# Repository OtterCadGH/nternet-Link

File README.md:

# nternet-Link

**An open-hardware platform that turns a TI-Nspire graphing calculator into a
networked handheld terminal.** It adds Wi-Fi, an AI chat/tutor, a camera that
reads and solves problems, and onboard storage, all through a small plug-in
device.

New to the Nspire scene? The spelling "nternet" is intentional. The Nspire's name plays on "inspire", and community projects follow suit by dropping the first letter, like the Ndless jailbreak playing on "endless". nternet is "internet", Nspire style.

Over four generations the project grew from a soldered-in modification into a
clean, reproducible, plug-in platform with a proper communication protocol and
custom PCBs.

[Discord](https://discord.gg/bBMqzaBu6B) · [Support on Ko-fi](https://ko-fi.com/nspired_hackers)

> **Not affiliated with or endorsed by Texas Instruments.** This is an
> embedded-systems and networking experiment. It is **not** designed or
> intended for use during exams. Follow your institution's rules.

---

## Try the calculator interface in your browser

The V4 calculator UI runs as a live simulator. The on-screen calculator and a
virtual ESP32 talk over the *real* V4 wire protocol, so you can experiment with
the whole experience before building anything.

**[Open the live simulator](https://ottercadgh.github.io/nternet-Link/v4/tools/gui_simulator.html)**,
or download [`v4/tools/gui_simulator.html`](v4/tools/gui_simulator.html) and
open it in any browser (it runs fully offline).

---

## Which version should I look at?

**Build [V4](v4/). It is the current, recommended generation.** The others are
here as history and reference.

| | Version | What it is | Build it? |
| --- | --- | --- | --- |
| 🟢 | **[V4](v4/)** | Rewritten firmware, protocol, and UI. Two custom PCBs: a full **camera** stick and a tiny **chat-only** board. Browser simulator, automated tests. | **Yes, start here** |
| ⚪ | [V3](v3/) | First ESP32-S3 and camera platform, with a host proxy server. | Superseded |
| ⚪ | [V2](v2/) | First external USB plug-in adapter (ESP32-C3). No calculator mod. | Superseded |
| ⚪ | [V1](v1/) | The original: an ESP32 soldered *inside* the calculator. | Legacy / reference |

---

## How it works

```
 TI-Nspire  =USB=>  nternet-Link device  =Wi-Fi=>  AI provider
 (keyboard,         (ESP32 + USB bridge             (Groq / OpenAI /
  screen, Lua)       + camera + SD)                  OpenRouter / local)
```

The calculator supplies the keyboard and screen and runs a Lua app. The device
is an ESP32 that bridges USB-serial to Wi-Fi, calls an AI API, drives a camera,
and stores photos and chat logs on a microSD card. In V4 the two sides speak
**nlink v1**, a framed protocol with CRC checks and automatic retries.

---

## Repository layout

```
README.md          you are here: the project hub
docs/              shared assets (hub images)
v1/                Ti-GPT, internal mod (legacy)
   firmware/       ESP32 .ino
   calculator/     Lua app + .tns
v2/                external adapter (docs)
v3/                ESP32-S3 and camera platform
   firmware/       ESP32 .ino
   calculator/     Lua app + .tns
   server/         host proxy server
v4/                CURRENT: the full rewrite
   README.md       tutorial and build guide (start here)
   src/ include/   ESP32 firmware (C++)
   calculator/     TI-Nspire Lua client + demo
   tools/          browser GUI simulator
   docs/           protocol spec
   test/           host-side tests
   hardware/       PCB design + 4 KiCad board variants
```

Each version folder has its own README. New here? Open [`v4/`](v4/).

---

## The story

**V1 (2025)** proved the concept by soldering an ESP32 onto the calculator's
USB lines. **V2** moved all the electronics *outside* into a plug-in adapter,
with no calculator modification. **V3** jumped to the ESP32-S3 with a camera
and a host proxy. **V4** is the ground-up rewrite: a reliable checksummed
protocol, no API keys in the source (they live in the device's flash), support
for any OpenAI-compatible AI provider, a browser simulator, automated tests,
and two custom circuit boards.

## Support

nternet-Link is a small side project, built in spare time and shared for free.
If it's been useful to you and you'd like to chip in, tips go toward parts and
the first run of ready made cables. No pressure at all, and thank you either way.

## License and spirit

Open hardware and software. Modify, improve, and share. Built for learning
about USB, serial protocols, embedded networking, and hardware interfacing.

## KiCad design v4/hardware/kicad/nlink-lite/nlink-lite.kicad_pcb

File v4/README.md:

# nternet-Link V4

**Turn a TI-Nspire graphing calculator into a networked handheld terminal.**
It adds Wi-Fi, an AI chat/tutor, a camera that reads and solves problems, and a
microSD card, all through a tiny plug-in device. No calculator modification.

V4 is a ground-up rewrite of the firmware, the calculator software, the
communication protocol, and the hardware, with two board designs: a full
camera stick and a tiny chat-only "stealth" version.

> **Not affiliated with Texas Instruments.** This is an embedded-systems and
> networking experiment. It is **not** designed or intended for use during
> exams. Follow your school's rules. Don't be that guy.

---

## Try it first: the calculator UI runs in your browser

Before you build anything, you can play with the exact interface the
calculator runs. This simulator is the *real* thing: the on-screen
calculator and a virtual ESP32 talk to each other over the actual V4 wire
protocol, byte for byte.

### [Open the live simulator](https://ottercadgh.github.io/nternet-Link/v4/tools/gui_simulator.html)

*(That live link works once GitHub Pages is enabled. See
[Publish the demo](#publish-the-demo-optional) below. Until then, download
[`tools/gui_simulator.html`](tools/gui_simulator.html) and double-click it.
It runs fully offline in any browser.)*

### What to try in it

1. **Click the calculator screen** to give it keyboard focus.
2. Press **`W`**, pick a Wi-Fi network, type any password, press **Enter**.
   (It's simulated, so any password "connects.")
3. Press **`T`**, type a question like `derivative of x^2`, press **Enter**,
   and watch the orange spark "think," then the answer stream in.
4. Press **Enter** on its own to "take a photo." A photo card appears and a
   solved problem streams back. Check the **SD card** panel: `IMG_0001.JPG`
   just appeared, exactly as it would on the real device.
5. Now break things on purpose with the **Virtual ESP32** panel:
   - **Corrupt next frame**: watch the wire log reject a bad packet and
     recover. This is the V4 protocol's error-checking working live.
   - **Force BUSY**, **API error**, **Drop WiFi**, **Unplug device**: see
     how the UI handles each.

The **Wire log** on the right shows every message between calculator and
device, decoded. That's the whole point of V4: a reliable, checksummed link.

---

## The four generations (and where V4 fits)

| Version | What it is | Status |
| ------- | ---------- | ------ |
| V1 Ti-GPT | ESP32 soldered *inside* the calculator | Legacy / historical |
| V2 nternet-Link | External USB plug-in adapter (ESP32-C3) | Works |
| V3 | ESP32-S3 plus camera, first modular platform | Superseded by V4 |
| **V4 (this)** | Rewritten firmware, protocol, and UI, two custom PCBs | **Current** |

**What V4 fixes from V3:** a proper checksummed packet protocol (no more
garbled responses), **no API keys baked into the source** (they live in the
device's flash, set from the calculator), support for any OpenAI-compatible AI
provider, and a clean, modular codebase with automated tests.

---

## How it works (the 30-second version)

```
 TI-Nspire  =USB=>  nternet-Link device  =Wi-Fi=>  AI provider
 (keyboard,         (ESP32 + USB bridge             (Groq / OpenAI /
  screen, Lua)       + camera + SD)                  OpenRouter / local)
```

The calculator runs a Lua app (its keyboard and screen). The device is an
ESP32 that bridges USB-serial to Wi-Fi, talks to an AI API, drives a camera,
and saves photos and chats to a microSD card. They communicate over **nlink
v1**, a small framed protocol with CRC checks and automatic retries
([full spec](docs/PROTOCOL.md)).

---

## Two boards to build

| | **nlink-cam** | **nlink-lite** |
| --- | --- | --- |
| MCU | ESP32-S3-PICO-1 (SiP) | ESP32-C3-MINI-1 |
| Features | AI chat **plus camera plus microSD** | AI chat only |
| Size | about 60 x 12.5 mm stick | about 38 x 16 mm, tiny |
| Use it for | The full experience | Minimal / discreet |

Both are in [`hardware/kicad/`](hardware/kicad/) as complete, netlist-verified
KiCad projects. Two more reference designs (`nlink-proto` on the S3-MINI-1
module, `nlink-stick` bare-chip) are included as build and de-risking variants.
See [`hardware/PCB-DESIGN.md`](hardware/PCB-DESIGN.md) for the full spec and
[`hardware/kicad/CAPTURE-PLAN.md`](hardware/kicad/CAPTURE-PLAN.md) for the
board internals.

---

## Build guide

### 1. Get the hardware

Start from a dev board to try everything before committing to a custom PCB.
A **Seeed XIAO ESP32-S3 (Sense)** gives you the S3, camera, and SD in one
module. You'll also need a **CP2102/CP2102N USB-UART bridge** and a
**USB-mini plug** to reach the calculator's port. Full parts list and wiring
in [`hardware/PCB-DESIGN.md`](hardware/PCB-DESIGN.md).

### 2. Flash the firmware

The firmware uses [PlatformIO](https://platformio.org/) (free VS Code
extension). Clone this folder, open it, and build the target for your board:

```bash
pio run -e xiao-s3    -t upload    # XIAO ESP32-S3 dev board (camera + SD)
pio run -e nlink-cam  -t upload    # custom camera PCB (ESP32-S3-PICO-1)
pio run -e nlink-lite -t upload    # custom chat-only PCB (ESP32-C3-MINI-1)
```

No secrets go in the code. You'll set your Wi-Fi and AI key **from the
calculator** in the next step.

### 3. Load the calculator app

Copy the Lua app onto your calculator with the free **TI-Nspire Student
Software** (or TiLP). The client library is
[`calculator/nlink.lua`](calculator/nlink.lua) and a ready-to-run app is
[`calculator/demo_app.lua`](calculator/demo_app.lua). Build them into a
`.tns` file and send it to the calculator.

### 4. First run

1. Plug the device into the calculator, open the app.
2. Get a free AI key (for example from [Groq](https://console.groq.com/keys)).
3. On the calculator, set it once. It's saved to the device's flash:
   ```
   CFG SET llm.key   YOUR_KEY_HERE
   CFG SET llm.base  https://api.groq.com/openai/v1
   ```
4. Press **`W`** to pick your Wi-Fi and enter the password.
5. Press **`T`** to ask a question, or **Enter** to snap a photo of a
   problem. Answers save to the SD card automatically.

Everything you'll see on screen is exactly what the
[browser simulator](#try-it-first-the-calculator-ui-runs-in-your-browser)
above shows.

---

## Repository layout

```
platformio.ini        firmware build targets
include/  src/         ESP32 firmware (C++): protocol, provisioning,
                       AI client, camera, SD storage
calculator/            TI-Nspire Lua client library + demo app
tools/gui_simulator.html   the browser demo above
docs/PROTOCOL.md       nlink v1 wire-protocol spec
test/                  host-side protocol tests (run on a PC)
hardware/              PCB design docs + 4 KiCad board variants
PROJECT-STATUS.md      current status and next steps
```

---

## Publish the demo (optional)

To make the browser simulator open from a link (so people can try it without
downloading), turn on **GitHub Pages**:

1. Repo **Settings**, then **Pages**.
2. **Build and deployment**, **Source: Deploy from a branch**.
3. Pick the branch this folder lives on and **/ (root)**, then **Save**.
4. After a minute, your simulator is live at:
   `https://ottercadgh.github.io/nternet-Link/v4/tools/gui_simulator.html`

Then the **Open the live simulator** button near the top of this page just
works.

---

## Status and roadmap

See [`PROJECT-STATUS.md`](PROJECT-STATUS.md). Short version: firmware,
protocol, simulator, and all four board schematics are done and verified.
Next up is finishing the custom-PCB layouts, porting the new UI onto the
calculator, and a first hardware bring-up.

## License and spirit

Open hardware and software. Modify, improve, and share. Built for learning
about USB, serial protocols, embedded networking, and hardware interfacing.

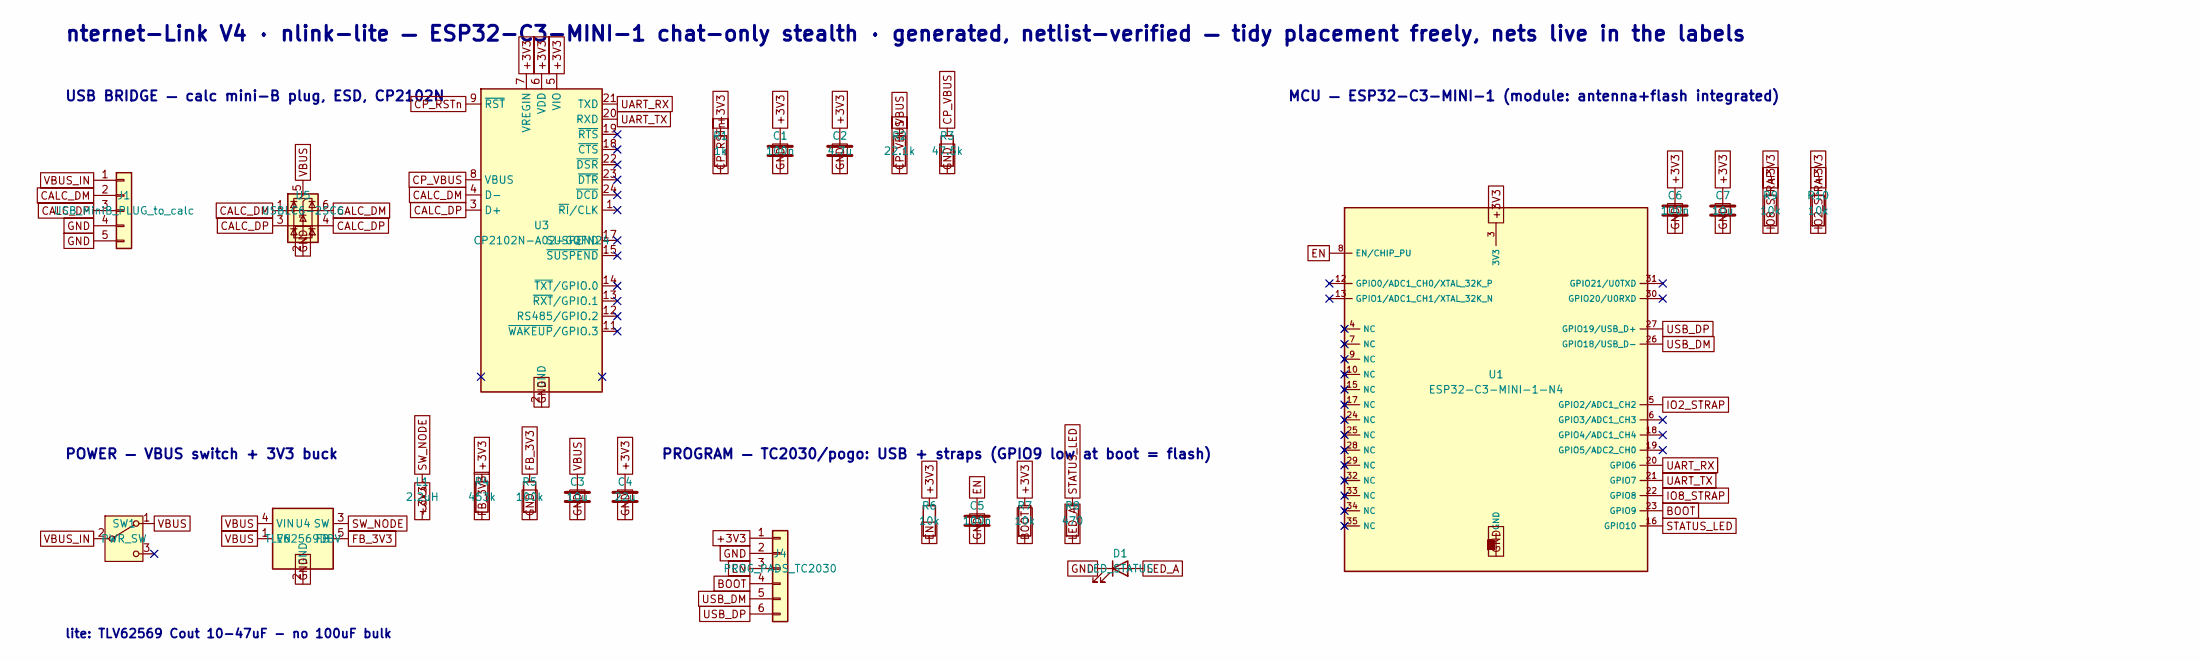
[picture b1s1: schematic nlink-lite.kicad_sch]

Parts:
C1, C5, C6: 100n; C_0402_1005Metric
C2: 4.7u; C_0402_1005Metric
C3, C7: 10u; C_0805_2012Metric
C4: 22u; C_0805_2012Metric
D1: LED_STATUS; LED_0402_1005Metric
J1: USB_MiniB_PLUG_to_calc; PinHeader_1x05_P2.54mm_Vertical; MPN mini-B male plug — see PCB-DESIGN.md op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
J4: PROG_PADS_TC2030; PinHeader_2x03_P1.27mm_Vertical_SMD
L1: 2.2uH; L_1210_3225Metric
R1: 1k; R_0402_1005Metric
R2: 22.1k; R_0402_1005Metric
R3: 47.5k; R_0402_1005Metric
R4: 453k; R_0402_1005Metric
R5: 100k; R_0402_1005Metric
R6, R7, R9, R10: 10k; R_0402_1005Metric
R8: 470; R_0402_1005Metric
SW1: PWR_SW; SW_SPDT_PCM12
U1: ESP32-C3-MINI-1-N4; ESP32-C3-MINI-1
U3: CP2102N-A02-GQFN24; QFN-24-1EP_4x4mm_P0.5mm_EP2.6x2.6mm
U4: TLV62569DBV; SOT-23-5
U5: USBLC6-2SC6; SOT-23-6

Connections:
+3V3: C1.1, C2.1, C4.1, C6.1, C7.1, J4.1, L1.2, R1.1, R4.1, R6.1, R7.1, R9.1, R10.1, U1.3 (3V3), U3.5 (VIO), U3.6 (VDD), U3.7 (VREGIN)
BOOT: J4.4, R7.2, U1.23 (GPIO9)
CALC_DM: J1.2, U3.4 (D-), U5.1 (I/O1), U5.6 (I/O1)
CALC_DP: J1.3, U3.3 (D+), U5.3 (I/O2), U5.4 (I/O2)
CP_RSTn: R1.2, U3.9 (~RST)
CP_VBUS: R2.2, R3.1, U3.8 (VBUS)
EN: C5.1, J4.3, R6.2, U1.8 (EN/CHIP_PU)
FB_3V3: R4.2, R5.1, U4.5 (FB)
GND: C1.2, C2.2, C3.2, C4.2, C5.2, C6.2, C7.2, D1.1 (K), J1.4, J1.5, J4.2, R3.2, R5.2, U1.1 (GND), U1.2 (GND), U1.11 (GND), U1.14 (GND), U1.36 (GND), U1.37 (GND), U1.38 (GND), U1.39 (GND), U1.40 (GND), U1.41 (GND), U1.42 (GND), U1.43 (GND), U1.44 (GND), U1.45 (GND), U1.46 (GND), U1.47 (GND), U1.48 (GND), U1.49 (GND), U1.50 (GND), U1.51 (GND), U1.52 (GND), U1.53 (GND), U3.2 (GND), U3.25 (GND), U4.2 (GND), U5.2 (GND)
IO2_STRAP: R10.2, U1.5 (GPIO2/ADC1_CH2)
IO8_STRAP: R9.2, U1.22 (GPIO8)
LED_A: D1.2 (A), R8.2
STATUS_LED: R8.1, U1.16 (GPIO10)
SW_NODE: L1.1, U4.3 (SW)
UART_RX: U1.20 (GPIO6), U3.21 (TXD)
UART_TX: U1.21 (GPIO7), U3.20 (RXD)
USB_DM: J4.5, U1.26 (GPIO18/USB_D-)
USB_DP: J4.6, U1.27 (GPIO19/USB_D+)
VBUS: C3.1, R2.1, SW1.1 (A), U4.1 (EN), U4.4 (VIN), U5.5 (VBUS)
VBUS_IN: J1.1, SW1.2 (B)

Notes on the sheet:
nternet-Link V4 · nlink-lite — ESP32-C3-MINI-1 chat-only stealth · generated, netlist-verified — tidy placement freely, nets live in the labels
USB BRIDGE — calc mini-B plug, ESD, CP2102N
POWER — VBUS switch + 3V3 buck
lite: TLV62569 Cout 10-47uF - no 100uF bulk
PROGRAM — TC2030/pogo: USB + straps (GPIO9 low at boot = flash)
MCU — ESP32-C3-MINI-1 (module: antenna+flash integrated)

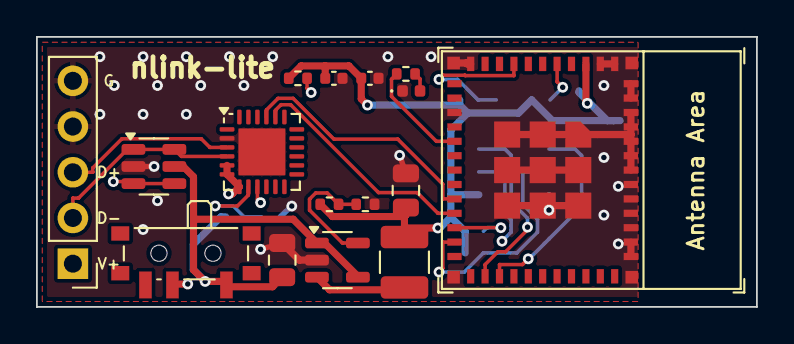
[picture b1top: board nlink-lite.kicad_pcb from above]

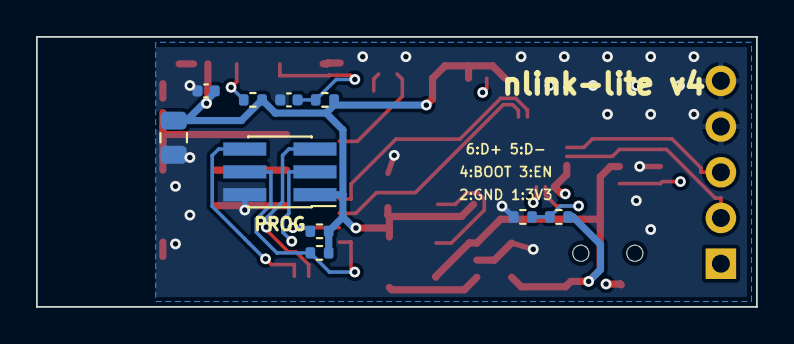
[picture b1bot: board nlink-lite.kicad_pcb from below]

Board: 4 copper layers, 40.0 x 15.0 mm, 26 parts (10 on the bottom side), 20 nets.

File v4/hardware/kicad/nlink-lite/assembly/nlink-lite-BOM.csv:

Comment,Designator,Footprint,Qty,MPN / spec,LCSC,Notes
100n,"C1,C5,C6",C_0402_1005Metric,3,100 nF 0402 X7R 16 V,,
4.7u,C2,C_0402_1005Metric,1,4.7 uF 0402 X5R 6.3 V,,
10u,"C3,C7",C_0805_2012Metric,2,10 uF 0805 X5R 16 V,,"C3 on 5 V VBUS, C7 at module"
22u,C4,C_0805_2012Metric,1,22 uF 0805 X5R 10 V,,buck output
LED_STATUS,D1,LED_0402_1005Metric,1,"0402 LED, any color, Vf <= 2.2 V",,GPIO10 via 470R
2.2uH,L1,L_1210_3225Metric,1,"2.2 uH, 1210, Isat >= 1.5 A, DCR <= 100 mOhm",,
1k,R1,R_0402_1005Metric,1,1k 0402 1% 1/16 W,,
22.1k,R2,R_0402_1005Metric,1,22.1k 0402 1% 1/16 W,,
47.5k,R3,R_0402_1005Metric,1,47.5k 0402 1% 1/16 W,,
453k,R4,R_0402_1005Metric,1,453k 0402 1% 1/16 W,,
100k,R5,R_0402_1005Metric,1,100k 0402 1% 1/16 W,,
10k,"R6,R7,R9,R10",R_0402_1005Metric,4,10k 0402 1% 1/16 W,,
470,R8,R_0402_1005Metric,1,470 0402 1% 1/16 W,,
PWR_SW,SW1,SW_SPDT_PCM12,1,C&K PCM12SMTR,,check current rating vs ~260 mA peak
ESP32-C3-MINI-1-N4,U1,ESP32-C3-MINI-1,1,Espressif ESP32-C3-MINI-1-N4,,PCB antenna at board edge
CP2102N-A02-GQFN24,U3,QFN-24-1EP_4x4mm_P0.5mm_EP2.6x2.6mm,1,Silicon Labs CP2102N-A02-GQFN24R,,
TLV62569DBV,U4,SOT-23-5,1,TI TLV62569DBVR,,"3.3 V buck, FB 453k/100k"
USBLC6-2SC6,U5,SOT-23-6,1,ST USBLC6-2SC6,,USB ESD
DNP,J1,,0,,,"mini-A plug pigtail, hand-soldered to 5 through-holes (pin 4 ID = GND)"
DNP,J4,,0,,,"pogo programming pads, no part"

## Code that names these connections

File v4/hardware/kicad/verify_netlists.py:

#!/usr/bin/env python3
"""Verify kicad-cli-exported netlists against the CAPTURE-PLAN net tables.

Assertions are written from the capture plan (component + pin NAME level),
independent of the generator's pin-number spec, so a wrong pin number or a
label that missed its pin shows up here as a failed net.
Usage: kicad-cli sch export netlist --output /tmp/X.net X.kicad_sch
       python3 verify_netlists.py /tmp/nlink-proto.net /tmp/nlink-stick.net
"""
import re, sys

def parse_netlist(path):
    text = open(path).read()
    nets = {}
    chunks = re.split(r'\(net \(code "\d+"\) \(name "([^"]+)"\)', text)
    # chunks: [prefix, name1, body1, name2, body2, ...]
    for i in range(1, len(chunks), 2):
        name, body = chunks[i], chunks[i + 1]
        nodes = set()
        for n in re.finditer(r'\(node \(ref "([^"]+)"\) \(pin "([^"]+)"\)'
                             r'(?: \(pinfunction "([^"]*)"\))?', body):
            ref, pin, func = n.groups()
            nodes.add((ref, pin, func or ""))
        nets[name] = nodes
    return nets

def has(nets, net, ref, pinfunc_re):
    """True if net contains a node of ref whose pinfunction matches regex."""
    for r, pin, func in nets.get(net, ()):
        if r == ref and re.fullmatch(pinfunc_re, func or pin):
            return True
    return False

failures = 0
def check(cond, msg):
    global failures
    print(("ok:   " if cond else "FAIL: ") + msg)
    if not cond: failures += 1

def verify(path, variant):
    global failures
    print(f"\n=== {path} ({variant}) ===")
    nets = parse_netlist(path)
    mcu = "U1"
    full = variant in ("mini", "bare", "cam")   # camera + SD present?

    # MCU-side pin-name expectations differ: S3 (mini/bare/cam) vs C3 (lite)
    if variant == "lite":
        TX, RX = "GPIO7", "GPIO6"
        USB_DP, USB_DM = r"GPIO19/USB_D\+", "GPIO18/USB_D-"
        LED = "GPIO10"                  # off the GPIO8 strap
        EN_PIN, IO0_PIN = "EN/CHIP_PU", "GPIO9"   # C3 boot strap is GPIO9
    else:
        TX, RX = "TXD0|U0TXD", "RXD0|U0RXD"
        USB_DP, USB_DM = r"IO20|GPIO20/USB_D\+", "IO19|GPIO19/USB_D-"
        LED = "IO1|GPIO1"
        EN_PIN, IO0_PIN = "EN|CHIP_PU", "IO0|GPIO0"

    # UART crossing: MCU TX -> bridge RXD, bridge TXD -> MCU RX
    check(has(nets, "UART_TX", "U3", "RXD") and has(nets, "UART_TX", mcu, TX),
          "UART_TX = MCU TX + bridge RXD (crossed once)")
    check(has(nets, "UART_RX", "U3", "TXD") and has(nets, "UART_RX", mcu, RX),
          "UART_RX = bridge TXD + MCU RX")

    # Calculator USB pair through ESD to bridge
    check(has(nets, "CALC_DP", "J1", "Pin_3") and has(nets, "CALC_DP", "U3", r"D\+")
          and has(nets, "CALC_DP", "U5", "I/O2"),
          "CALC_DP: plug pin3 + ESD + bridge D+")
    check(has(nets, "CALC_DM", "J1", "Pin_2") and has(nets, "CALC_DM", "U3", "D-")
          and has(nets, "CALC_DM", "U5", "I/O1"),
          "CALC_DM: plug pin2 + ESD + bridge D-")

    # Power chain: plug VBUS -> switch -> buck VIN; buck feedback divider
    check(has(nets, "VBUS_IN", "J1", "Pin_1") and has(nets, "VBUS_IN", "SW1", "B"),
          "VBUS_IN: plug pin1 -> switch common")
    check(has(nets, "VBUS", "SW1", "A") and has(nets, "VBUS", "U4", "VIN")
          and has(nets, "VBUS", "U4", "EN") and has(nets, "VBUS", "U5", "VBUS"),
          "VBUS: switch -> buck VIN+EN, ESD VBUS")
    check(has(nets, "SW_NODE", "U4", "SW") and has(nets, "SW_NODE", "L1", ".*"),
          "SW_NODE: buck SW -> inductor")
    check(has(nets, "FB_3V3", "U4", "FB"), "FB divider present on buck FB")
    check(has(nets, "+3V3", "U3", "VDD") and has(nets, "+3V3", "U3", "VREGIN"),
          "+3V3 powers bridge VDD+VREGIN (self-powered config)")

    if full:
        # SD (SPI mode) + pull-ups
        for net, sdfunc, mfunc in [("SD_CS", "DAT3/CD", "IO21|GPIO21"),
                                   ("SD_MOSI", "CMD", "IO9|GPIO9"),
                                   ("SD_SCK", "CLK", "IO7|GPIO7"),
                                   ("SD_MISO", "DAT0", "IO8|GPIO8")]:
            check(has(nets, net, "J3", sdfunc) and has(nets, net, mcu, mfunc),
                  f"{net}: SD {sdfunc} <-> MCU {mfunc}")
        check(sum(1 for r, _, _ in nets.get("SD_CS", ()) if r.startswith("R")) == 1 and
              sum(1 for r, _, _ in nets.get("SD_MISO", ()) if r.startswith("R")) == 1,
              "SD_CS and SD_MISO have pull-ups")

        # Camera DVP mapping (MCU side per final GPIO allocation)
        cam = {"CAM_XCLK": "IO10|GPIO10", "CAM_SIOD": "IO40|MTDO",
               "CAM_SIOC": "IO39|MTCK", "CAM_VSYNC": "IO38|GPIO38",
               "CAM_HREF": "IO47|SPICLK_P", "CAM_PCLK": "IO13|GPIO13",
               "CAM_Y2": "IO15|XTAL_32K_P", "CAM_Y3": "IO17|GPIO17",
               "CAM_Y4": "IO18|GPIO18", "CAM_Y5": "IO16|XTAL_32K_N",
               "CAM_Y6": "IO14|GPIO14", "CAM_Y7": "IO12|GPIO12",
               "CAM_Y8": "IO11|GPIO11", "CAM_Y9": "IO48|SPICLK_N"}
        for net, func in cam.items():
            check(has(nets, net, mcu, func) and has(nets, net, "J2", ".*"),
                  f"{net}: MCU {func} <-> camera FPC")
        check(all(has(nets, n, r, ".*") for n, r in
                  [("CAM_SIOD", "R"), ("CAM_SIOC", "R")]
                  for r in [x for x, _, _ in nets.get(n, ()) if x.startswith("R")][:1]),
              "SCCB pull-ups on SIOD/SIOC")

    # Programming pads: native USB + straps
    check(has(nets, "USB_DP", mcu, USB_DP) and has(nets, "USB_DP", "J4", "Pin_6"),
          "USB_DP: MCU USB_D+ -> prog pad 6")
    check(has(nets, "USB_DM", mcu, USB_DM) and has(nets, "USB_DM", "J4", "Pin_5"),
          "USB_DM: MCU USB_D- -> prog pad 5")
    check(has(nets, "EN", mcu, EN_PIN) and has(nets, "EN", "J4", "Pin_3"),
          "EN: MCU enable -> prog pad 3 (+RC)")
    BOOT = "BOOT" if variant == "lite" else "IO0"
    check(has(nets, BOOT, mcu, IO0_PIN) and has(nets, BOOT, "J4", "Pin_4")
          and any(r.startswith("R") for r, _, _ in nets.get(BOOT, ())),
          f"{BOOT}: boot strap {IO0_PIN} -> prog pad 4 (+pull-up)")
    check(has(nets, "STATUS_LED", mcu, LED), "STATUS_LED wired")

    # GND sanity: every IC grounded
    gnd_refs = ["U1", "U3", "U4", "U5", "J1"] + (["J3"] if full else [])
    for ref in gnd_refs:
        check(any(r == ref for r, _, _ in nets.get("GND", ())),
              f"GND reaches {ref}")

    if variant == "lite":
        check(has(nets, "GND", "J1", "Pin_4"),
              "J1 ID pin grounded (Nspire host mode / VBUS on)")
        check(has(nets, "CP_VBUS", "U3", "VBUS") and not has(nets, "VBUS", "U3", "VBUS")
              and sum(1 for r, _, _ in nets.get("CP_VBUS", ()) if r.startswith("R")) == 2,
              "CP2102N VBUS sense through resistor divider")
        for net, func in [("IO8_STRAP", "GPIO8"), ("IO2_STRAP", r"GPIO2/.*")]:
            check(has(nets, net, mcu, func)
                  and any(r.startswith("R") for r, _, _ in nets.get(net, ())),
                  f"{net}: {func} strap pulled up")
        check(not any(r == mcu and f.startswith("GPIO0") for name, n in nets.items()
                      if not name.startswith("unconnected-") for r, _, f in n),
              "GPIO0 unused (not a C3 strap)")

    if variant in ("bare", "cam"):
        check(has(nets, "RF_FEED", mcu, "LNA_IN"), "RF: LNA_IN -> pi match")
        check(has(nets, "ANT_FEED", "ANT1", "FEED"), "RF: pi match -> antenna")

    if variant == "bare":
        # flash on VDD_SPI + SPI0 pins
        for net, ff, mf in [("FLASH_CS", "~{CS}", "SPICS0"),
                            ("FLASH_CLK", "CLK", "SPICLK"),
                            ("FLASH_D", r"DI\(IO0\)", "SPID"),
                            ("FLASH_Q", r"DO\(IO1\)", "SPIQ"),
                            ("FLASH_WP", "IO2", "SPIWP"),
                            ("FLASH_HD", "IO3", "SPIHD")]:
            check(has(nets, net, "U2", ff) and has(nets, net, mcu, mf),
                  f"{net}: flash {ff} <-> MCU {mf}")
        check(has(nets, "VDD_SPI", "U2", "VCC") and has(nets, "VDD_SPI", mcu, "VDD_SPI"),
              "flash powered from VDD_SPI")
        check(has(nets, "XTAL_P", "Y1", ".*") and has(nets, "XTAL_P", mcu, "XTAL_P"),
              "crystal XTAL_P wired")

print("nlink netlist verification")
VARIANTS = [("mini", "/tmp/nlink-proto.net"), ("bare", "/tmp/nlink-stick.net"),
            ("cam", "/tmp/nlink-cam.net"), ("lite", "/tmp/nlink-lite.net")]
import os
for variant, path in VARIANTS:
    if os.path.exists(path):
        verify(path, variant)
print(f"\n{'FAILURES: ' + str(failures) if failures else 'All netlist checks passed.'}")
sys.exit(1 if failures else 0)

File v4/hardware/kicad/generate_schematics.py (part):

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def add_program(sch, ctx, j4_fp="Connector:Tag-Connect_TC2030-IDC-FP_2x03_P1.27mm_Vertical",
                boot_net="IO0"):
    # --- programming pads + straps + LED -------------------------------------
    pin = "GPIO9" if boot_net == "BOOT" else "IO0"
    sch.text(f"PROGRAM — TC2030/pogo: USB + straps ({pin} low at boot = flash)", (130, 82), 1.7)
    sch.place("J4", "Connector_Generic", "Conn_01x06", "PROG_PADS_TC2030",
              j4_fp,
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    c3gnd = {str(n): "GND" for n in
             [1, 2, 11, 14, 36, 37, 38, 39, 40, 41, 42, 43, 44, 45, 46, 47,
              48, 49, 50, 51, 52, 53]}
    # Straps (ESP32-C3 datasheet): GPIO9 low at reset = download boot (weak
    # internal pull-up); GPIO8 must be high for download boot and floats at
    # reset; GPIO2 floats, pull-up recommended. GPIO0 is NOT a C3 strap.
    # Status LED moved off the GPIO8 strap to GPIO10.
    sch.place("U1", "nlink_parts", "ESP32-C3-MINI-1", "ESP32-C3-MINI-1-N4",
              "Espressif:ESP32-C3-MINI-1", (270, 70),
              {"3": "+3V3", "8": "EN", "23": "BOOT", "16": "STATUS_LED",
               "22": "IO8_STRAP", "5": "IO2_STRAP",
               "21": "UART_TX", "20": "UART_RX",   # GPIO7 tx, GPIO6 rx
               "26": "USB_DM", "27": "USB_DP",      # GPIO18/19 native USB
               **c3gnd})
    # decoupling AT the module 3V3 pin (place within ~2 mm of pin 3)
    ctx.rcl("C", "100n", (300, 40), "+3V3", "GND")
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
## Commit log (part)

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2026-01-23 Rename README.md to README.V2.md
2026-01-23 Rename README.V2 to README.V2.md
2026-02-09 Rename README.V1.md to V1_Ti-GPT.md
2026-02-11 Create Ti-GPT.V1.lua
    Raw lua for chatgpt demo on v1 and v2 builds. Directly upload .tns file if you dont want to bother with the lua side of things
2026-03-26 Update V2_nternet-Link.md
    3d files added
